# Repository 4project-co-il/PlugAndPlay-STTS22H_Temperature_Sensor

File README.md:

# PlugAndPlay: Module with STTS22H Temperature Sensor
This is the repository with the files for PlugAndPlay module with STTS22H Temperature Sensor.

The STTS22H is accessible via the I2C channel, with ALERT/INT pin connected to INT1 line.

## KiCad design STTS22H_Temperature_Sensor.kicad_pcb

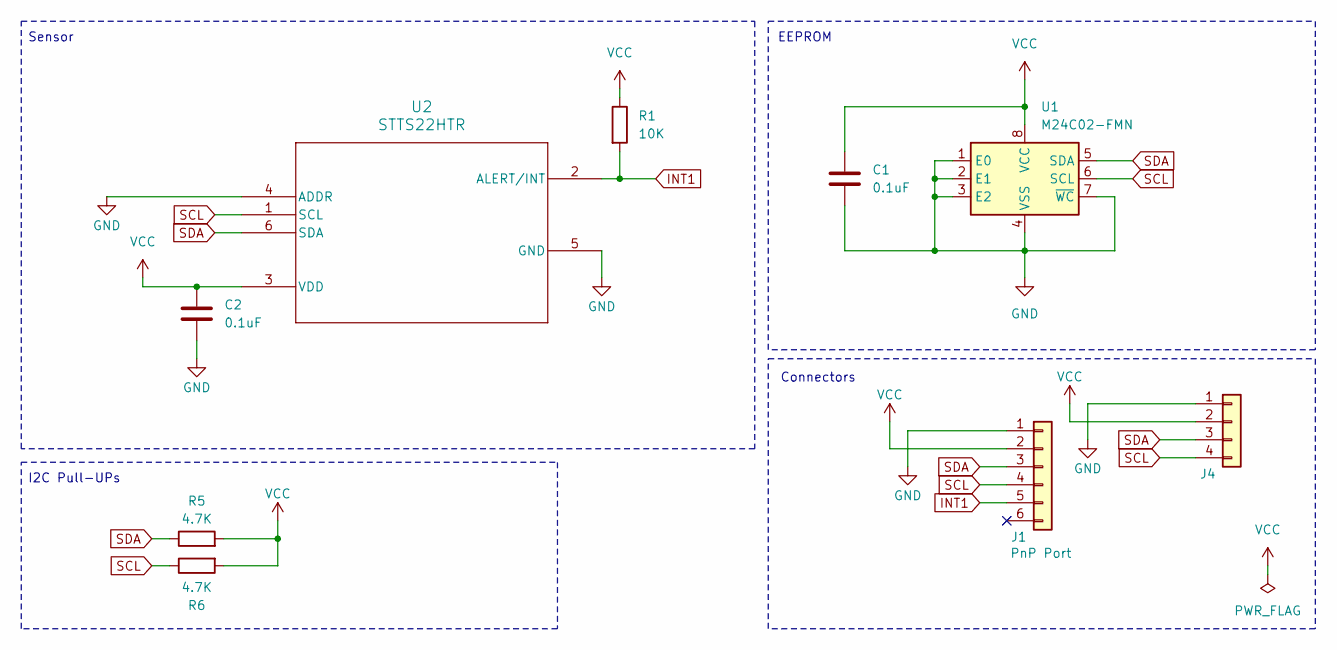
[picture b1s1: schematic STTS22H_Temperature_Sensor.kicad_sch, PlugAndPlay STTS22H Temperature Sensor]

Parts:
C1, C2: 0.1uF; C_0603_1608Metric; MPN C14663
J1: JST_SH_SM06B-SRSS-TB_1x06-1MP_P1.00mm_Horizontal; MPN C7430448
J4: Conn_01x04; PogoPinsPads_1x04_P2.5mm
R1: 10K; R_0603_1608Metric_Pad0.98x0.95mm_HandSolder; MPN C25804
R5, R6: 4.7K; R_0603_1608Metric; MPN C4190
U1: M24C02-FMN; SOIC-8_3.9x4.9mm_P1.27mm; MPN C114502
U2: STTS22HTR; UDFN-6L_2X2X0P5_STM

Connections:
GND: C1.2, C2.2, J1.1, J4.1, U1.1 (E0), U1.2 (E1), U1.3 (E2), U1.4 (VSS), U1.7 (~WC), U2.4 (ADDR), U2.5 (GND), U2.7
INT1: J1.5, R1.2, U2.2 (ALERT/INT)
SCL: J1.4, J4.4, R6.1, U1.6 (SCL), U2.1 (SCL)
SDA: J1.3, J4.3, R5.1, U1.5 (SDA), U2.6 (SDA)
VCC: C1.1, C2.1, J1.2, J4.2, R1.1, R5.2, R6.2, U1.8 (VCC), U2.3 (VDD)

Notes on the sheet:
EEPROM
Sensor
Connectors
I2C Pull-UPs

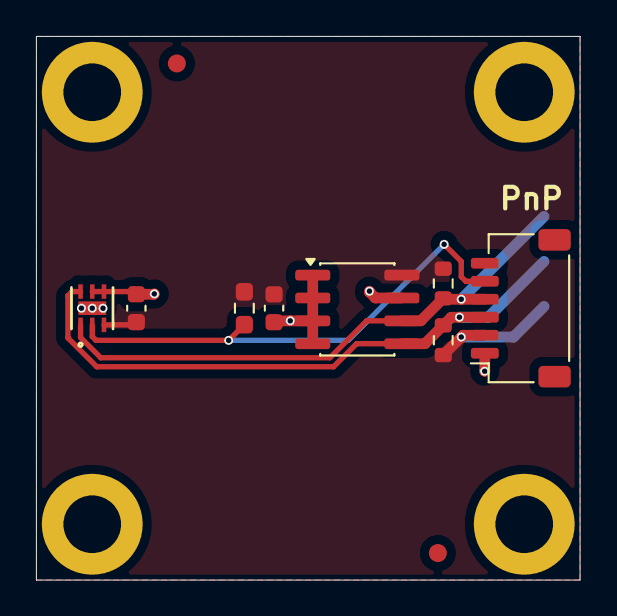
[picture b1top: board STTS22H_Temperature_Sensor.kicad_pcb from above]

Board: 2 copper layers, 30.2 x 30.2 mm, 9 parts (1 on the bottom side), 5 nets.
